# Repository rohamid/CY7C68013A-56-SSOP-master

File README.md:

# CY7C68013A 56 SSOP dev board

# Fix this:
* EEPROM connection's. I made a mistake for EERPOM address connection. Pin no.1 should be connected to EEPROM enable jumper.
* USB connector (if you gonna use usb C, don't do manual soldering. It doesn't really that strong, but if you gonna give it to PCBA I think it will gonna do it. Don't know why)
* Try black tactile button, it feel better

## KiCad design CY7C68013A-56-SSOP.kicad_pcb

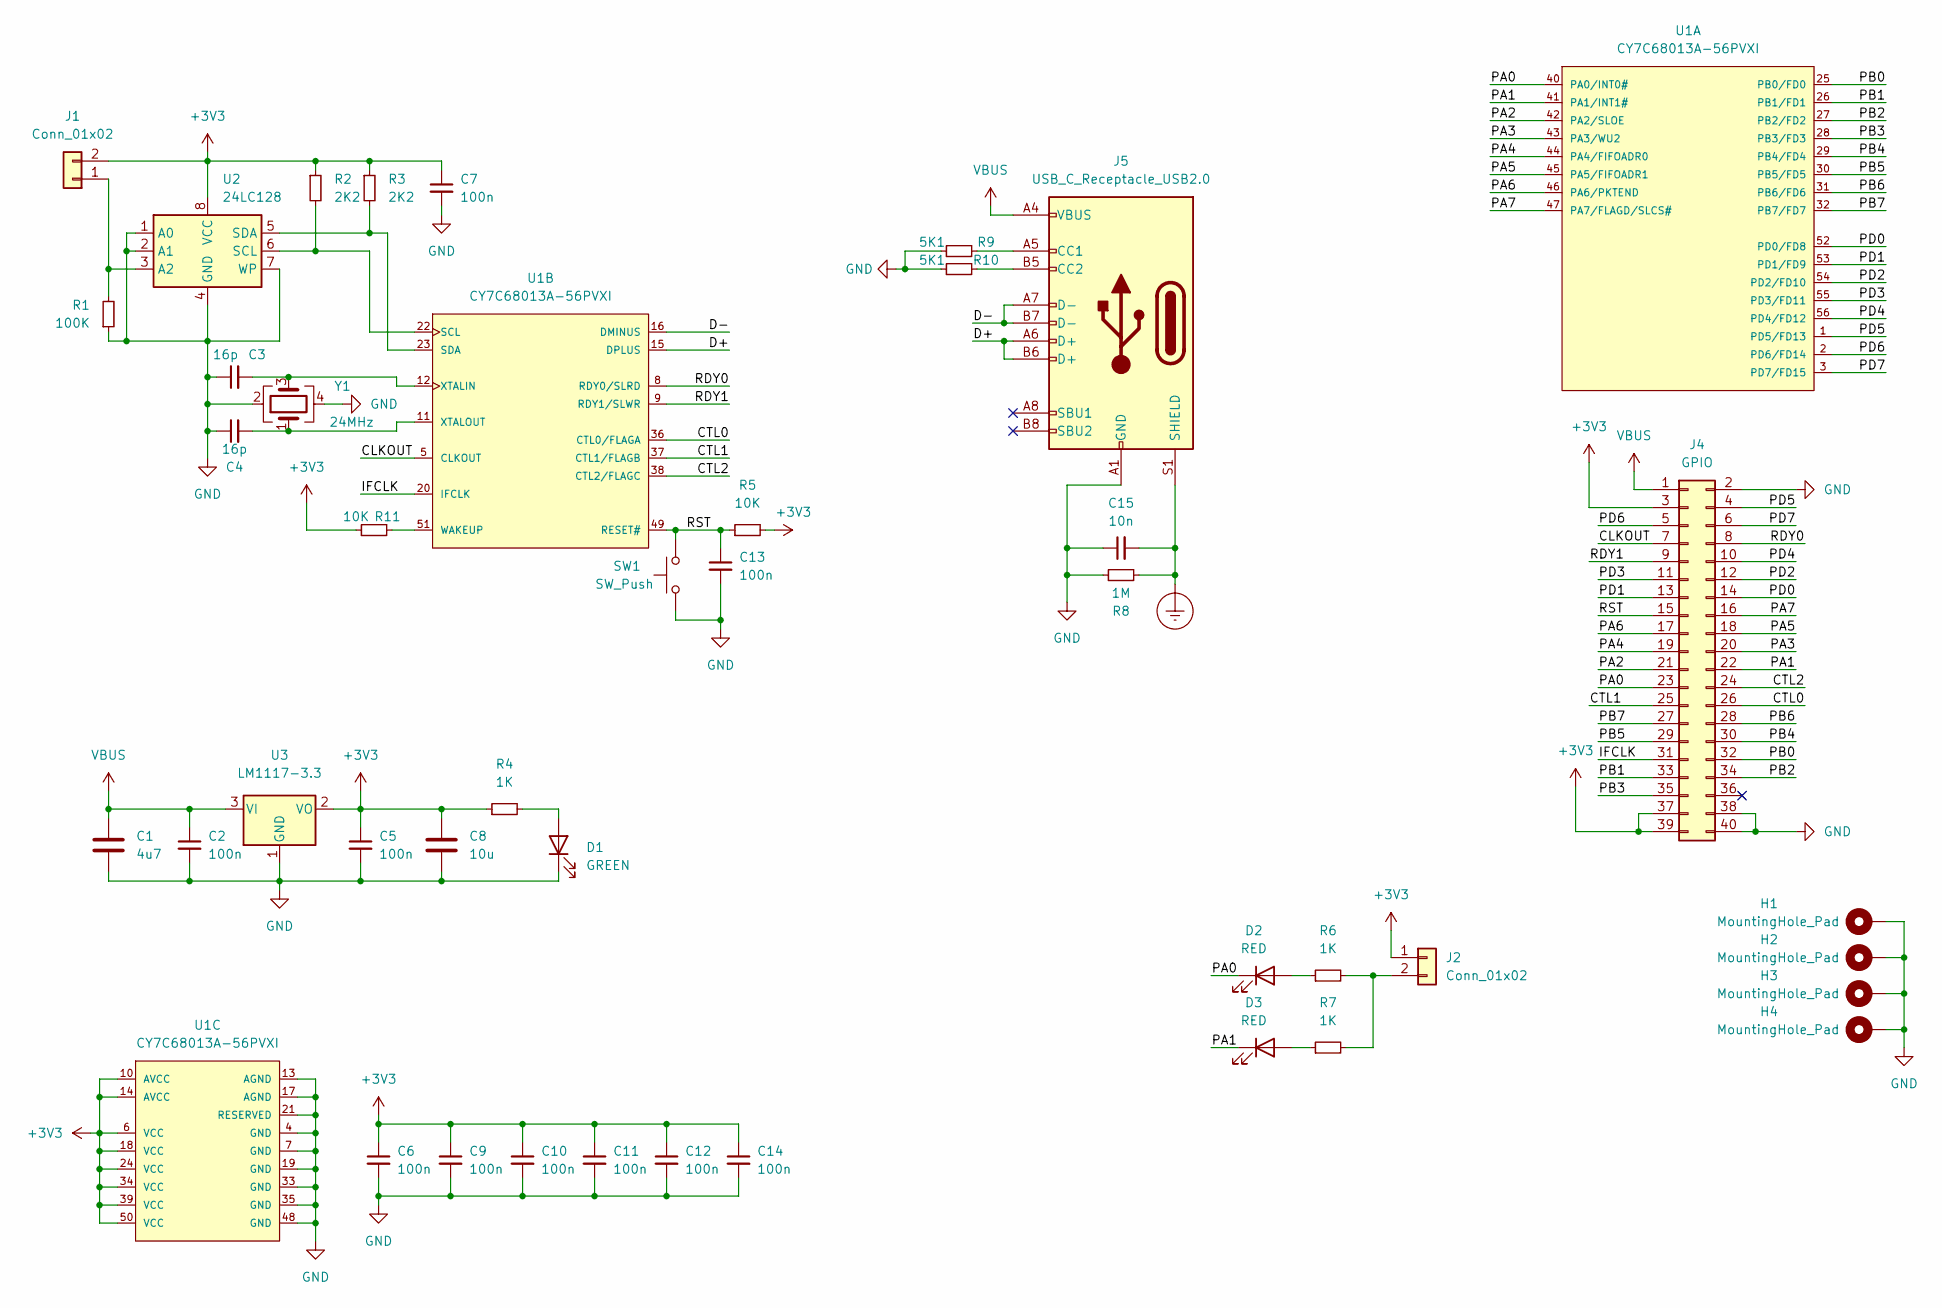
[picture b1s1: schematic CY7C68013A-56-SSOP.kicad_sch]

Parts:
C1: 4u7; C_0805_2012Metric; LCSC Part Number C1779
C2, C5, C6, C7, C9, C10, C11, C12, C13, C14: 100n; C_0402_1005Metric; LCSC Part Number C307331
C3, C4: 16p; C_0402_1005Metric; LCSC Part Number C1547
C8: 10u; C_0805_2012Metric; LCSC Part Number C15850
C15: 10n; C_0805_2012Metric; LCSC Part Number C106840
D1: GREEN; LED_0805_2012Metric; LCSC Part Number C34499
D2, D3: RED; LED_0805_2012Metric; LCSC Part Number C84256
H1, H2, H3, H4: MountingHole_Pad; MountingHole_3.2mm_M3_Pad_Via
J1, J2: Conn_01x02; PinHeader_1x02_P2.54mm_Vertical
J4: GPIO; PinHeader_2x20_P2.54mm_Horizontal
J5: USB_C_Receptacle_USB2.0; USB_C_Receptacle_G-Switch_GT-USB-7010ASV
R1: 100K; R_0402_1005Metric; LCSC Part Number C25741
R2, R3: 2K2; R_0402_1005Metric; LCSC Part Number C25879
R4, R6, R7: 1K; R_0402_1005Metric; LCSC Part Number C11702
R5: 10K; R_0402_1005Metric; LCSC Part Number C25744
R8: 1M; R_0402_1005Metric; LCSC Part Number C26083
R9, R10: 5K1; R_0402_1005Metric; LCSC Part Number C25744
R11: 10K; R_0402_1005Metric; LCSC Part Number C11702
SW1: SW_Push; SW_Push_1P1T_NO_CK_KMR2; LCSC Part Number C115360
U1: CY7C68013A-56PVXI; SSOP-56_7.5x18.5mm_P0.635mm; LCSC Part Number CY7C68013A-56PVXC
U2: 24LC128; SOIC-8_3.9x4.9mm_P1.27mm; LCSC Part Number C81195
U3: LM1117-3.3; SOT-223-3_TabPin2; LCSC Part Number C6186
Y1: 24MHz; Crystal_SMD_3225-4Pin_3.2x2.5mm; LCSC Part Number C2650460

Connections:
+3V3: C5.1, C6.1, C7.1, C8.1, C9.1, C10.1, C11.1, C12.1, C14.1, J1.2, J2.1, J4.3, J4.37, J4.39, R2.1, R3.1, R4.1, R5.2, R11.1, U1.6 (VCC), U1.10 (AVCC), U1.14 (AVCC), U1.18 (VCC), U1.24 (VCC), U1.34 (VCC), U1.39 (VCC), U1.50 (VCC), U2.8 (VCC), U3.2 (VO); also elsewhere on the board
/CLKOUT: J4.7, U1.5 (CLKOUT)
/CTL0: J4.26, U1.36 (CTL0/FLAGA)
/CTL1: J4.25, U1.37 (CTL1/FLAGB)
/CTL2: J4.24, U1.38 (CTL2/FLAGC)
/D+: J5.A6 (D+), J5.B6 (D+), U1.15 (DPLUS)
/D-: J5.A7 (D-), J5.B7 (D-), U1.16 (DMINUS)
/IFCLK: J4.31, U1.20 (IFCLK)
/PA0: D2.1 (K), J4.23, U1.40 (PA0/INT0#)
/PA1: D3.1 (K), J4.22, U1.41 (PA1/INT1#)
/PA2: J4.21, U1.42 (PA2/SLOE)
/PA3: J4.20, U1.43 (PA3/WU2)
/PA4: J4.19, U1.44 (PA4/FIFOADR0)
/PA5: J4.18, U1.45 (PA5/FIFOADR1)
/PA6: J4.17, U1.46 (PA6/PKTEND)
/PA7: J4.16, U1.47 (PA7/FLAGD/SLCS#)
/PB0: J4.32, U1.25 (PB0/FD0)
/PB1: J4.33, U1.26 (PB1/FD1)
/PB2: J4.34, U1.27 (PB2/FD2)
/PB3: J4.35, U1.28 (PB3/FD3)
/PB4: J4.30, U1.29 (PB4/FD4)
/PB5: J4.29, U1.30 (PB5/FD5)
/PB6: J4.28, U1.31 (PB6/FD6)
/PB7: J4.27, U1.32 (PB7/FD7)
/PD0: J4.14, U1.52 (PD0/FD8)
/PD1: J4.13, U1.53 (PD1/FD9)
/PD2: J4.12, U1.54 (PD2/FD10)
/PD3: J4.11, U1.55 (PD3/FD11)
/PD4: J4.10, U1.56 (PD4/FD12)
/PD5: J4.4, U1.1 (PD5/FD13)
/PD6: J4.5, U1.2 (PD6/FD14)
/PD7: J4.6, U1.3 (PD7/FD15)
/RDY0: J4.8, U1.8 (RDY0/SLRD)
/RDY1: J4.9, U1.9 (RDY1/SLWR)
/RST: C13.1, J4.15, R5.1, SW1.2, U1.49 (RESET#)
Earth_Protective: C15.2, J5.S1 (SHIELD), R8.2
GND: C1.2, C2.2, C3.1, C4.1, C5.2, C6.2, C7.2, C8.2, C9.2, C10.2, C11.2, C12.2, C13.2, C14.2, C15.1, D1.1 (K), H1.1, H2.1, H3.1, H4.1, J4.2, J4.38, J4.40, J5.A1 (GND), J5.A12 (GND), J5.B1 (GND), J5.B12 (GND), R1.1, R8.1, R9.1, R10.1, SW1.1, U1.4 (GND), U1.7 (GND), U1.13 (AGND), U1.17 (AGND), U1.19 (GND), U1.21 (RESERVED), U1.33 (GND), U1.35 (GND), U1.48 (GND), U2.1 (A0), U2.2 (A1), U2.4 (GND), U2.7 (WP), U3.1 (GND), Y1.2, Y1.4; also elsewhere on the board
unnamed: C3.2, U1.12 (XTALIN), Y1.3
unnamed: C4.2, U1.11 (XTALOUT), Y1.1
unnamed: D1.2 (A), R4.2
unnamed: D2.2 (A), R6.1
unnamed: D3.2 (A), R7.1
unnamed: J1.1, R1.2, U2.3 (A2)
unnamed: J2.2, R6.2, R7.2
unnamed: J5.A5 (CC1), R9.2
unnamed: J5.B5 (CC2), R10.2
unnamed: R2.2, U1.22 (SCL), U2.6 (SCL)
unnamed: R3.2, U1.23 (SDA), U2.5 (SDA)
unnamed: R11.2, U1.51 (WAKEUP)
VBUS: C1.1, C2.1, J4.1, J5.A4 (VBUS), J5.A9 (VBUS), J5.B4 (VBUS), J5.B9 (VBUS), U3.3 (VI); also elsewhere on the board

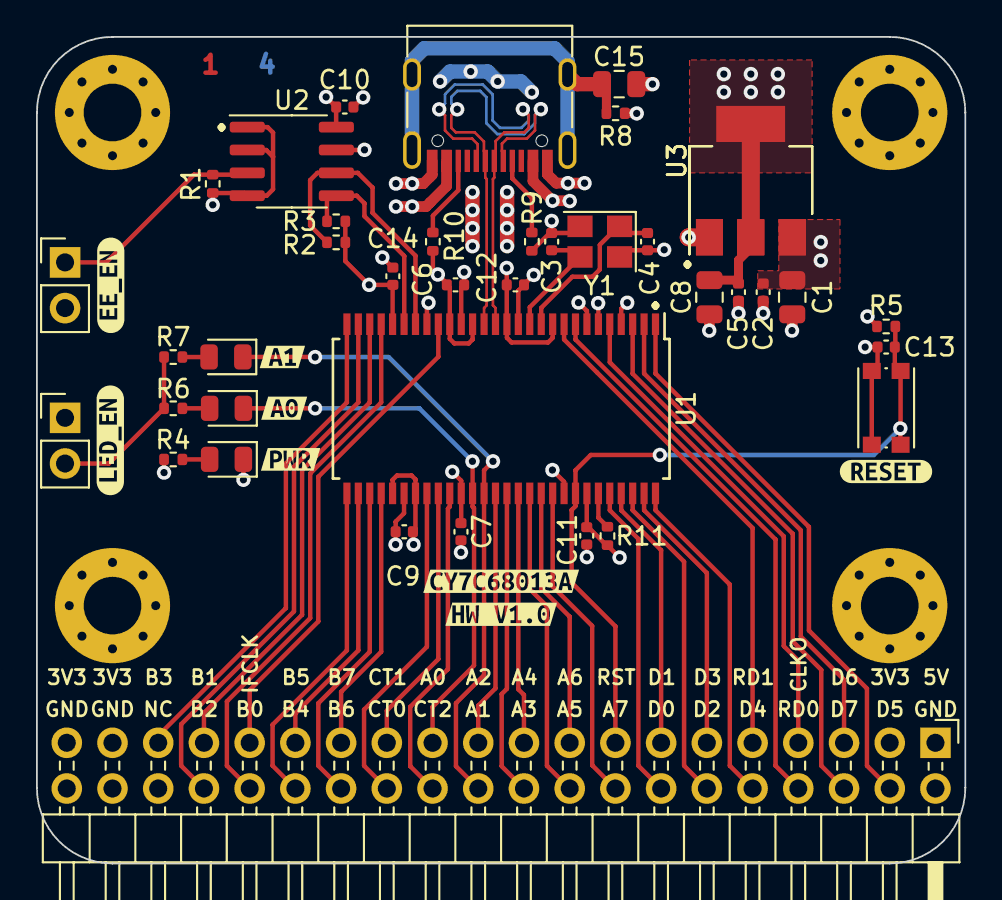
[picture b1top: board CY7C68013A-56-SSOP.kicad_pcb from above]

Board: 4 copper layers, 51.6 x 45.9 mm, 51 parts (0 on the bottom side), 50 nets.

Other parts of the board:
U3#2: LM1117-3.3; SOT-223-3_TabPin2
kibuzzard-63EC9D7C: G***; kibuzzard-63EC9D7C
kibuzzard-63EC9D86: G***; kibuzzard-63EC9D86
kibuzzard-63F2CE48: G***; kibuzzard-63F2CE48
kibuzzard-63F2CE91: G***; kibuzzard-63F2CE91
kibuzzard-63F33066: G***; kibuzzard-63F33066
kibuzzard-63FDD9FB: G***; kibuzzard-63FDD9FB
kibuzzard-63FDDA02: G***; kibuzzard-63FDDA02
kibuzzard-63FDDA26: G***; kibuzzard-63FDDA26

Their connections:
+3V3: U3#2.2 (VO); also elsewhere on the board
GND: U3#2.1 (GND); also elsewhere on the board
VBUS: U3#2.3 (VI); also elsewhere on the board
